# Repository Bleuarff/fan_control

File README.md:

# Fan Control

Control fan speed based on temperature

* Arduino source for PWM on fan depending on temperature
* Eagle schematics for shield PCB

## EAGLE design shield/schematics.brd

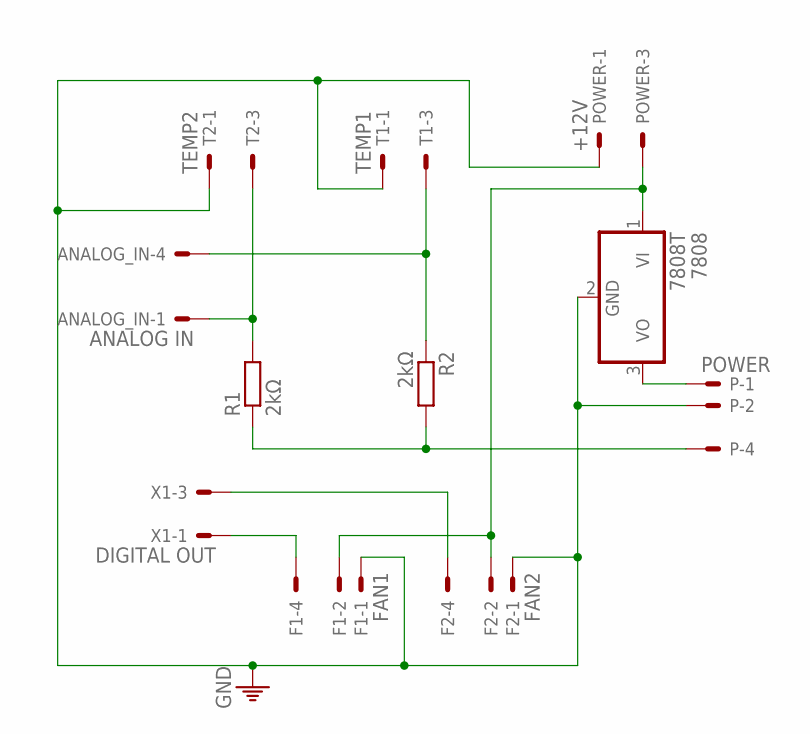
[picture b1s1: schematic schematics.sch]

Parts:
7808: 7808T; TO220H
ANALOG_IN: ANALOG IN; 22-23-2041
F1: FAN1; 22-23-2041
F2: FAN2; 22-23-2041
P: POWER; 22-23-2041
POWER: +12V; 22-23-2031
R1, R2: 2kΩ; 0411/15
T1: TEMP1; 22-23-2031
T2: TEMP2; 22-23-2031
X1: DIGITAL OUT; 22-23-2031

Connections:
unnamed: F1.4, X1.1
unnamed: F2.4, X1.3
unnamed: P.4, R1.1, R2.2
unnamed: 7808.3 (VO), P.1
unnamed: 7808.1 (VI), F1.2, F2.2, POWER.3
unnamed: ANALOG_IN.4, R2.1, T1.3
unnamed: ANALOG_IN.1, R1.2, T2.3
PE: 7808.2 (GND), F1.1, F2.1, P.2, POWER.1, T1.1, T2.1

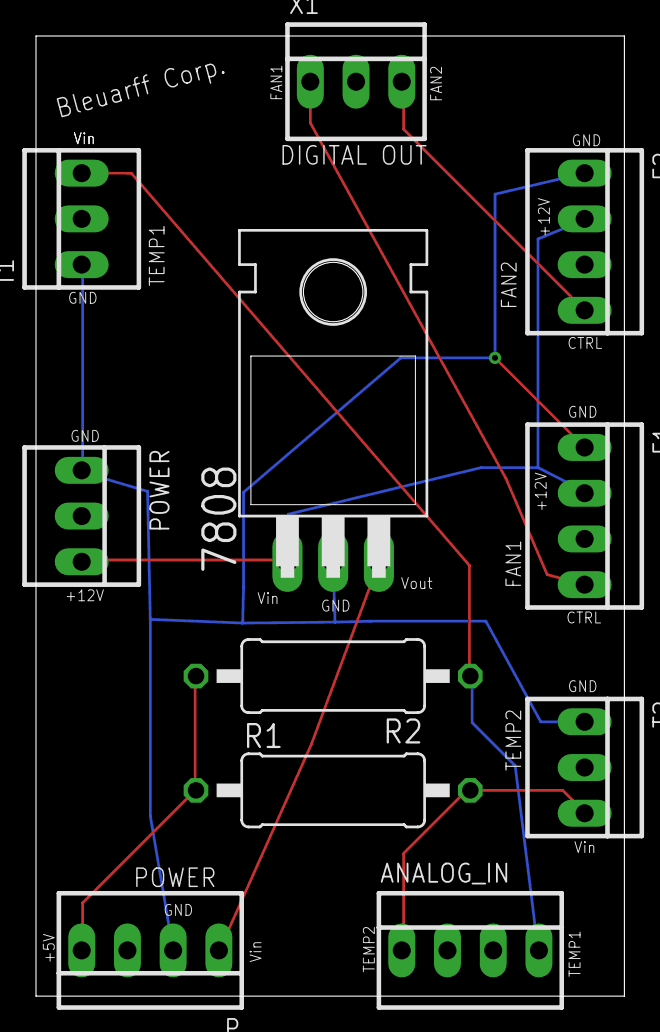
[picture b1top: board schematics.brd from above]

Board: 2 copper layers, 32.7 x 53.3 mm, 11 parts (0 on the bottom side), 8 nets.

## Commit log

2016-02-20 First version of script
2016-02-20 change pin numbers
2016-07-31 Production version!
    - source code ok
    - Eagle schematics used for pcb
